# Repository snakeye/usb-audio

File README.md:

# USB Audio

* PCM2705
* MAX9724

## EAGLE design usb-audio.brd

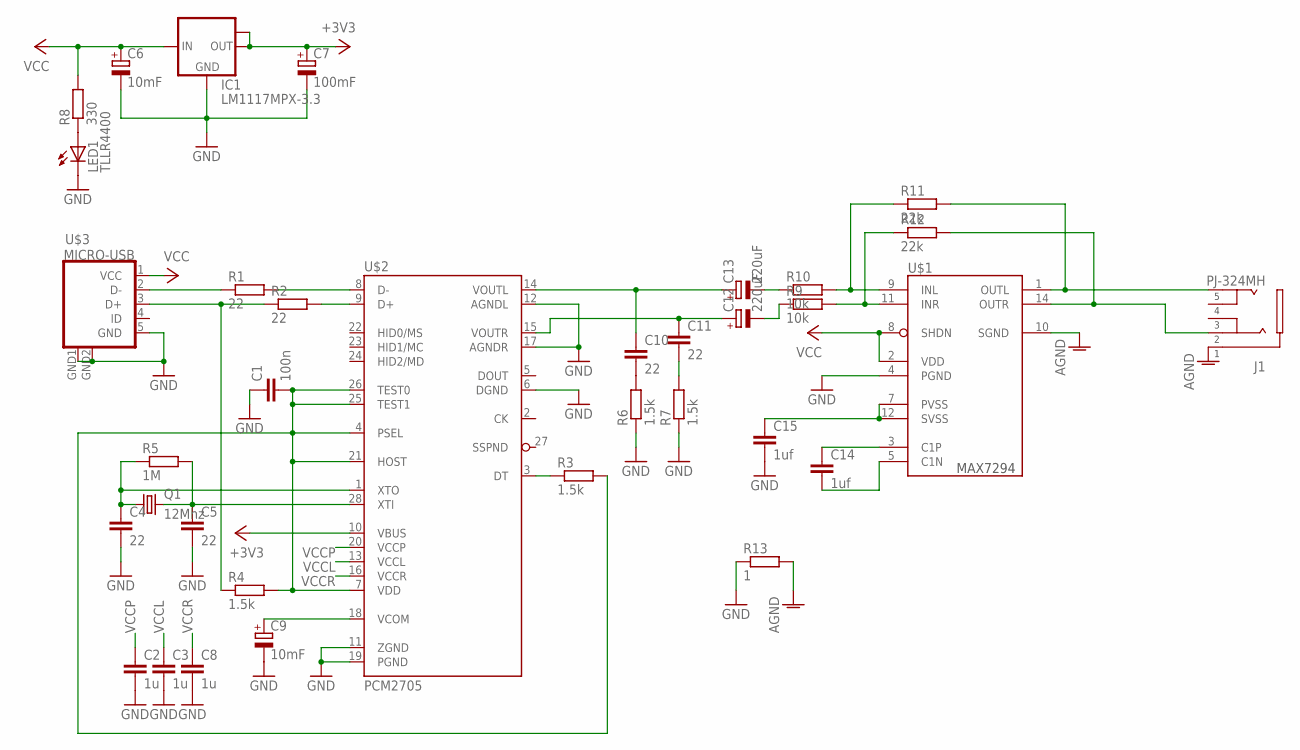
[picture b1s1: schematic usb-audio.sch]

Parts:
C1: 100n; C0805
C2, C3, C8: 1u; C0805
C4, C5, C10, C11: 22; C0805
C6, C9: 10mF; CT3216
C7: 100mF; CT3216
C12, C13: 220uF; E2-5
C14, C15: 1uf; C0805
IC1: LM1117MPX-3.3; SOT223
J1: PJ-324MH
LED1: TLLR4400; LED3MM
Q1: 12Mhz; HC49/S
R1, R2: 22; R0805
R3, R4, R6, R7: 1.5k; R0805
R5: 1M; R0805
R8: 330; R0805
R9, R10: 10k; R0805
R11, R12: 22k; R0805
R13: 1; R0805
U$1: MAX9724AEUD+; TSSOP14
U$2: PCM2705; SSOP28
U$3: MICRO-USB

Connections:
+3V3: C7.+, IC1.2 (OUT), IC1.TAB (OUT1), U$2.10 (VBUS)
AGND: J1.1, R13.2, U$1.10 (SGND)
GND: C1.1, C2.2, C3.2, C4.2, C5.2, C6.-, C7.-, C8.2, C9.-, C15.2, IC1.1 (GND), LED1.K (C), R6.1, R7.1, R13.1, U$1.4 (PGND), U$2.6 (DGND), U$2.11 (ZGND), U$2.12 (AGNDL), U$2.17 (AGNDR), U$2.19 (PGND), U$3.5 (GND), U$3.GND1 (GND), U$3.GND2 (GND)
unnamed: R1.2, U$2.8 (D-)
unnamed: R2.2, U$2.9 (D+)
unnamed: C9.+, U$2.18 (VCOM)
unnamed: R3.1, U$2.3 (DT)
unnamed: R1.1, U$3.2 (D-)
unnamed: R2.1, R4.1, U$3.3 (D+)
unnamed: C5.1, Q1.2, R5.2, U$2.28 (XTI)
unnamed: C4.1, Q1.1, R5.1, U$2.1 (XTO)
unnamed: C14.1, U$1.3 (C1P)
unnamed: C14.2, U$1.5 (C1N)
unnamed: J1.5, R11.2, U$1.1 (OUTL)
unnamed: J1.2, R12.2, U$1.14 (OUTR)
unnamed: C15.1, U$1.7 (PVSS), U$1.12 (SVSS)
unnamed: C1.2, R3.2, R4.2, U$2.4 (PSEL), U$2.7 (VDD), U$2.21 (HOST), U$2.25 (TEST1), U$2.26 (TEST0)
unnamed: C10.2, R6.2
unnamed: C11.2, R7.2
unnamed: C11.1, C12.+, U$2.15 (VOUTR)
unnamed: C12.-, R9.1
unnamed: C13.-, R10.1
unnamed: C10.1, C13.+, U$2.14 (VOUTL)
unnamed: LED1.A, R8.1
unnamed: R10.2, R11.1, U$1.9 (INL)
unnamed: R9.2, R12.1, U$1.11 (INR)
VCC: C6.+, IC1.3 (IN), R8.2, U$1.2 (VDD), U$1.8 (SHDN), U$3.1 (VCC)
VCCL: C3.1, U$2.13 (VCCL)
VCCP: C2.1, U$2.20 (VCCP)
VCCR: C8.1, U$2.16 (VCCR)

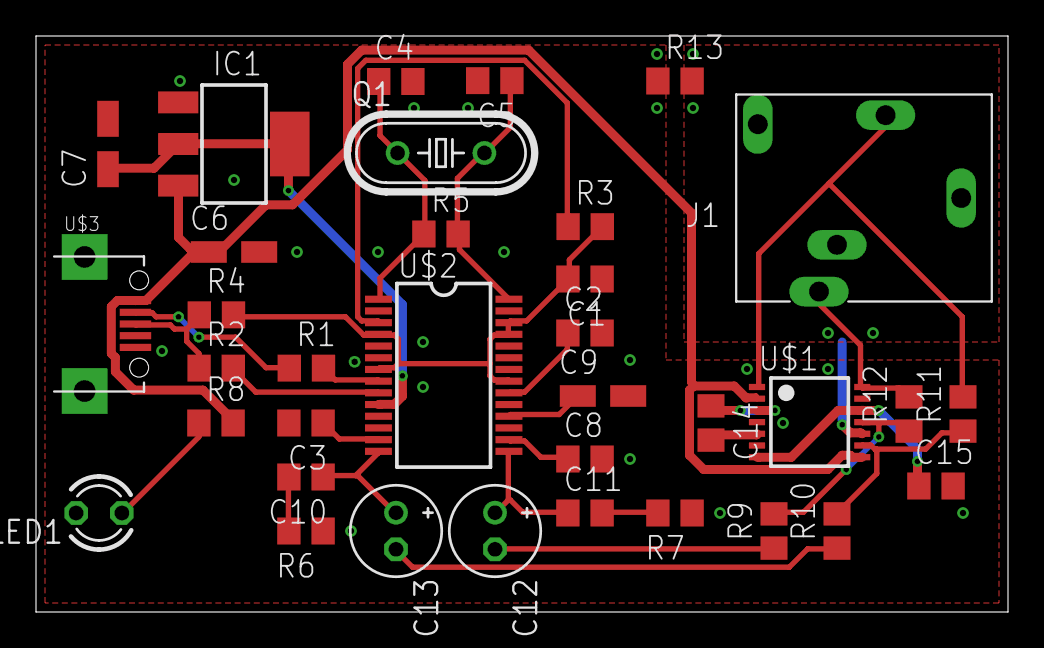
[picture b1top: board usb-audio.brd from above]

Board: 2 copper layers, 54.0 x 32.0 mm, 35 parts (0 on the bottom side), 30 nets.

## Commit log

2018-02-07 rev 1
2018-03-10 Updated values
